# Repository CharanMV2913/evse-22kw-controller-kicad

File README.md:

# 22 kW EVSE controller project

The repository now contains the prototype implementation specification, safety-state-machine guidance, release checklist, and initial KiCad board outline.

This is an engineering prototype baseline, not a certified charger. The next mandatory step is exact component selection and schematic capture against the chosen external Type A + RDC-DD or Type B protection assembly. The board must remain SELV/control-only; do not add 415 V conductors to it.

See `docs/implementation-spec.md` and `docs/release-checklist.md` before ordering boards.

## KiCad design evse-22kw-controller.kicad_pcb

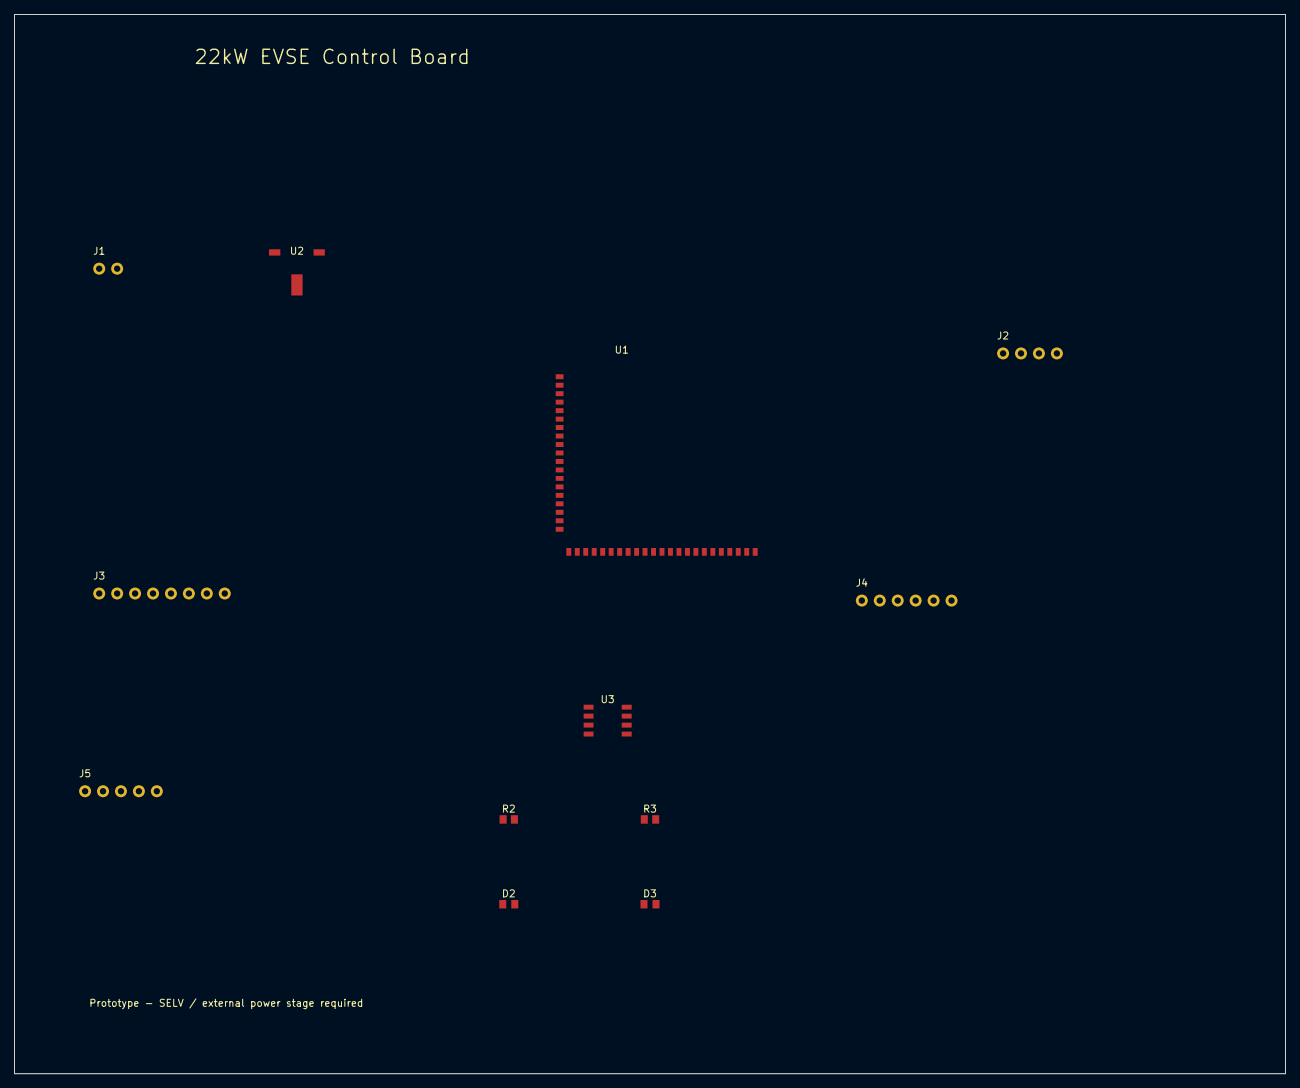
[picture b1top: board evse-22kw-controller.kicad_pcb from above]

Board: 2 copper layers, 180.0 x 150.0 mm, 12 parts (0 on the bottom side), 8 nets, no tracks yet.

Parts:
D2, D3: LED_0603_1608Metric
J1: Molex_KK-254_AE-6410-02A_1x02_P2.54mm_Vertical
J2: Molex_KK-254_AE-6410-04A_1x04_P2.54mm_Vertical
J3: Molex_KK-254_AE-6410-08A_1x08_P2.54mm_Vertical
J4: Molex_KK-254_AE-6410-06A_1x06_P2.54mm_Vertical
J5: Molex_KK-254_AE-6410-05A_1x05_P2.54mm_Vertical
R2, R3: R_0603_1608Metric
U1: ESP32-S3-WROOM-1
U2: SOT-223-3_TabPin2
U3: SOIC-8_3.9x4.9mm_P1.27mm

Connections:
0V_SELV: D2.1, D3.1, J1.2, J2.4, J3.8, J4.3, J4.4, J4.5, J4.6, J5.5, R2.2, R3.2, U1.1, U1.9, U1.10, U1.11, U1.12, U1.13, U1.14, U1.15, U1.16, U1.17, U1.18, U1.19, U1.20, U1.21, U1.22, U1.24, U1.25, U1.26, U1.27, U1.28, U1.29, U1.30, U1.31, U1.32, U1.33, U1.34, U1.35, U1.36, U1.37, U1.38, U1.39, U1.40, U1.41, U1.42, U2.1, U3.1, U3.2, U3.3, U3.5, U3.6, U3.7
+3V3: D2.2, D3.2, R2.1, R3.1, U1.2, U1.23, U2.2, U3.8
+24V_SELV: J1.1, J2.1, U2.3
GPIO4: J5.3, U1.4, U3.4
GPIO5: J5.4, U1.5
GPIO7: U1.7, U1.8
RCD_STATUS: J3.1, J3.2
SAFETY_OK: J2.3, J3.4, J3.5, J3.6, J3.7, U1.3
